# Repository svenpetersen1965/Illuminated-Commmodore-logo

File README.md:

# Illuminated-Commodore-logo
This is, what you need for your hobby retro computer projects: a Commodore logo, which is illuminated with two LEDs!

This project consists out of a 3D printed logo and a PCB that contains the LEDs and limiting resistors. 

The 3D print is made from three parts:
1. The illuminated body, which is printed with transparent PLA
2. A face plate
3. A reflector

The transparent part is printed with 100% infill (important!). I have printed it upright (on the side with the LED holes). 

There are two types of face plates: one with rounded corners and one without. It should be printed from a material, that is not any translucent. Black is a good color. White is not so suitable. 

The orientation of the reflector while printng is not so important. It should be printed with a white filament.

The Fusion 360 design is contained in this project.

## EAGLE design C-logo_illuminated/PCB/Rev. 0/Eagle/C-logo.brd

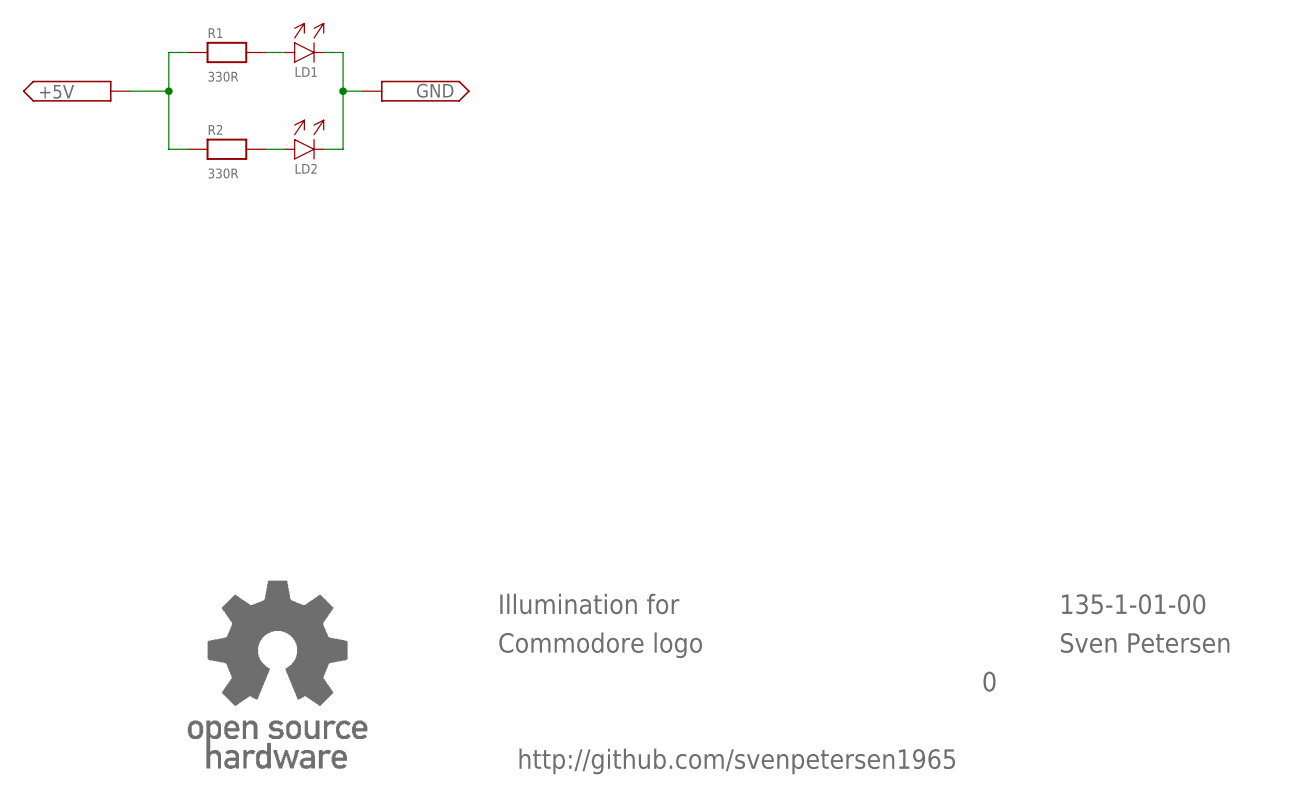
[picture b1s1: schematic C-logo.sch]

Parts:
+5V: PAD1,0/AUTO; 1.0/AUTO
GND: PAD1,0/AUTO; 1.0/AUTO
LD1, LD2: 5MM90°INSERTED; 5MM_90°
R1, R2: 330R; R-10
U$5: OPEN_SOURCE_HW; OPENHW

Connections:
GND: +5V.1, R1.1, R2.1
unnamed: LD1.A, R1.2
unnamed: LD2.A, R2.2
unnamed: GND.1, LD1.K, LD2.K

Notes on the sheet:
Illumination for
Commodore logo
135-1-01-00
Sven Petersen
http://github.com/svenpetersen1965

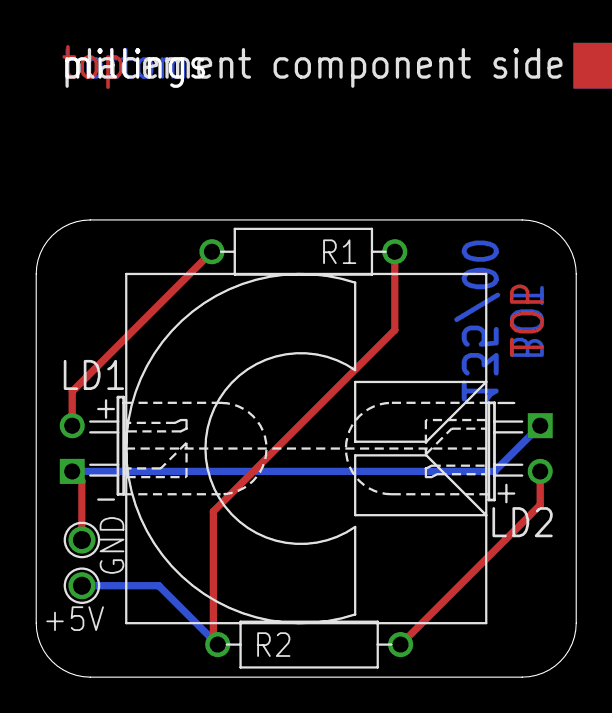
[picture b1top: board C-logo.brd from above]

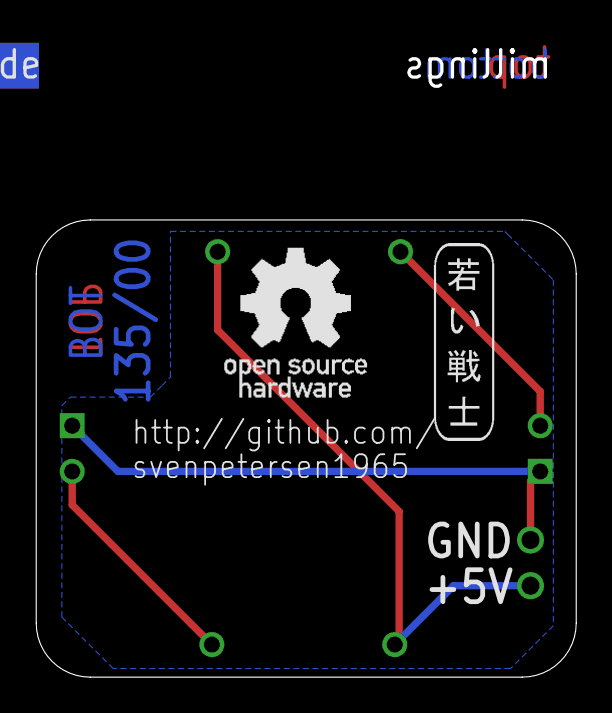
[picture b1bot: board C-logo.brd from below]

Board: 2 copper layers, 30.0 x 35.6 mm, 10 parts (2 on the bottom side), 4 nets.

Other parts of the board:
U$2: 2LAYER
U$3: SVEN_TAG
U$4: PCB-TITLE/

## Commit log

2020-08-08 Silk Screen updated
2020-08-08 Silk Screen Update
